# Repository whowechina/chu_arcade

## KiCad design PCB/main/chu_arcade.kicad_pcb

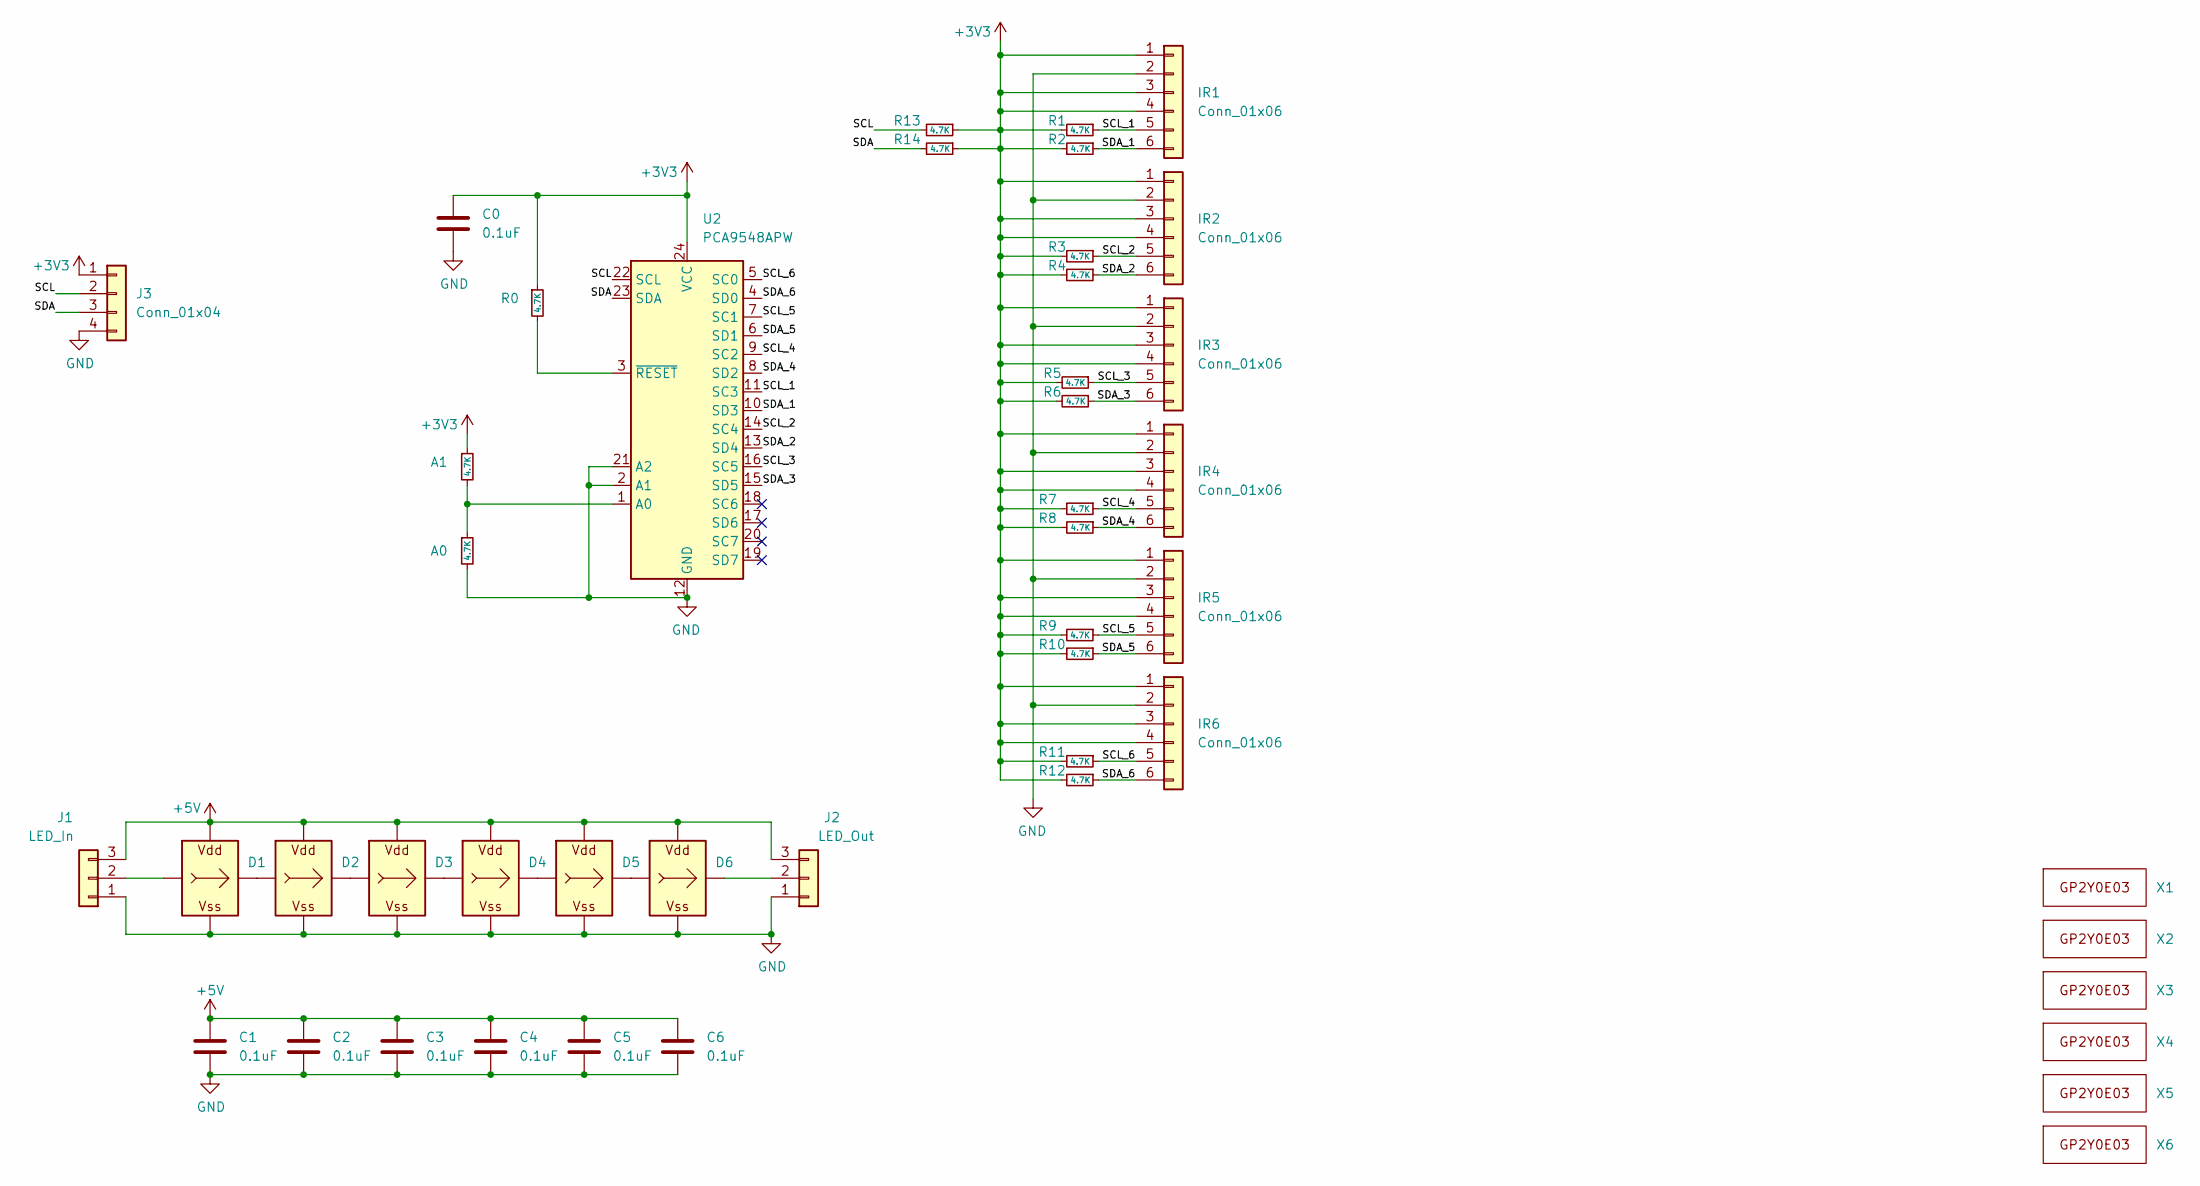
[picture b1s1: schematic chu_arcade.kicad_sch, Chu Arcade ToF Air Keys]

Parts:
A0, A1: 4.7K; R_0603_1608Metric; LCSC C23186
C0, C1, C2, C3, C4, C5, C6: 0.1uF; C_0603_1608Metric_Pad1.08x0.95mm_HandSolder
D1, D2, D3, D4, D5, D6: WS2812B_Unified; WS2812B-4020
IR1, IR2, IR3, IR4, IR5, IR6: Conn_01x06; GP2Y0E03
J1: LED_In; Solder_3P
J2: LED_Out; Solder_3P
J3: Conn_01x04; Solder_4P
R0, R1, R2, R3, R4, R5, R6, R7, R8, R9, R10, R11, R12, R13, R14: 4.7K; R_0603_1608Metric; LCSC C23186
U2: PCA9548APW; TSSOP-24_4.4x7.8mm_P0.65mm
X1, X2, X3, X4, X5, X6: GP2Y0E03_REAL

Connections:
+3V3: A1.1, C0.1, IR1.1, IR1.3, IR1.4, IR2.1, IR2.3, IR2.4, IR3.1, IR3.3, IR3.4, IR4.1, IR4.3, IR4.4, IR5.1, IR5.3, IR5.4, IR6.1, IR6.3, IR6.4, J3.1, R0.1, R1.2, R2.2, R3.2, R4.2, R5.2, R6.2, R7.2, R8.2, R9.2, R10.2, R11.2, R12.2, R13.1, R14.1, U2.24 (VCC)
+5V: C1.1, C2.1, C3.1, C4.1, C5.1, C6.1, D1.V (VDD), D2.V (VDD), D3.V (VDD), D4.V (VDD), D5.V (VDD), D6.V (VDD), J1.3, J2.3
/SCL: J3.2, R13.2, U2.22 (SCL)
/SCL_1: IR1.5, R1.1, U2.11 (SC3)
/SCL_2: IR2.5, R3.1, U2.14 (SC4)
/SCL_3: IR3.5, R5.1, U2.16 (SC5)
/SCL_4: IR4.5, R7.1, U2.9 (SC2)
/SCL_5: IR5.5, R9.1, U2.7 (SC1)
/SCL_6: IR6.5, R11.1, U2.5 (SC0)
/SDA: J3.3, R14.2, U2.23 (SDA)
/SDA_1: IR1.6, R2.1, U2.10 (SD3)
/SDA_2: IR2.6, R4.1, U2.13 (SD4)
/SDA_3: IR3.6, R6.1, U2.15 (SD5)
/SDA_4: IR4.6, R8.1, U2.8 (SD2)
/SDA_5: IR5.6, R10.1, U2.6 (SD1)
/SDA_6: IR6.6, R12.1, U2.4 (SD0)
GND: A0.2, C0.2, C1.2, C2.2, C3.2, C4.2, C5.2, C6.2, D1.G (VSS), D2.G (VSS), D3.G (VSS), D4.G (VSS), D5.G (VSS), D6.G (VSS), IR1.2, IR2.2, IR3.2, IR4.2, IR5.2, IR6.2, J1.1, J2.1, J3.4, U2.2 (A1), U2.12 (GND), U2.21 (A2)
unnamed: D1.I (In), J1.2
unnamed: D1.O (Out), D2.I (In)
unnamed: D2.O (Out), D3.I (In)
unnamed: D3.O (Out), D4.I (In)
unnamed: D4.O (Out), D5.I (In)
unnamed: D5.O (Out), D6.I (In)
unnamed: D6.O (Out), J2.2
unnamed: A0.1, A1.2, U2.1 (A0)
unnamed: R0.2, U2.3 (~RESET)

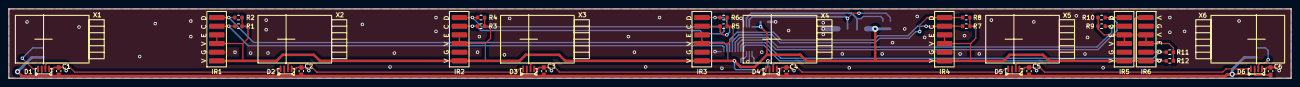
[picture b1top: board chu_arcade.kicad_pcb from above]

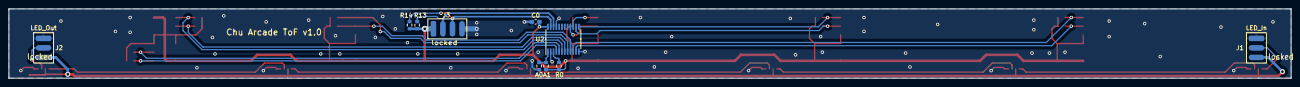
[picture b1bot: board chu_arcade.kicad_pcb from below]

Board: 2 copper layers, 296.0 x 16.0 mm, 46 parts (10 on the bottom side), 26 nets.

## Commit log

2024-02-25 Initial upload
2024-02-25 Chunithm complains wrong IO board
2024-02-27 Fixed IO4 issue
2024-03-02 Add I2C main pull-up resistors
2024-03-09 Fix air tower switch order
2024-03-13 Remove aime code
2025-01-02 Compiled UF2 in firmware folder
